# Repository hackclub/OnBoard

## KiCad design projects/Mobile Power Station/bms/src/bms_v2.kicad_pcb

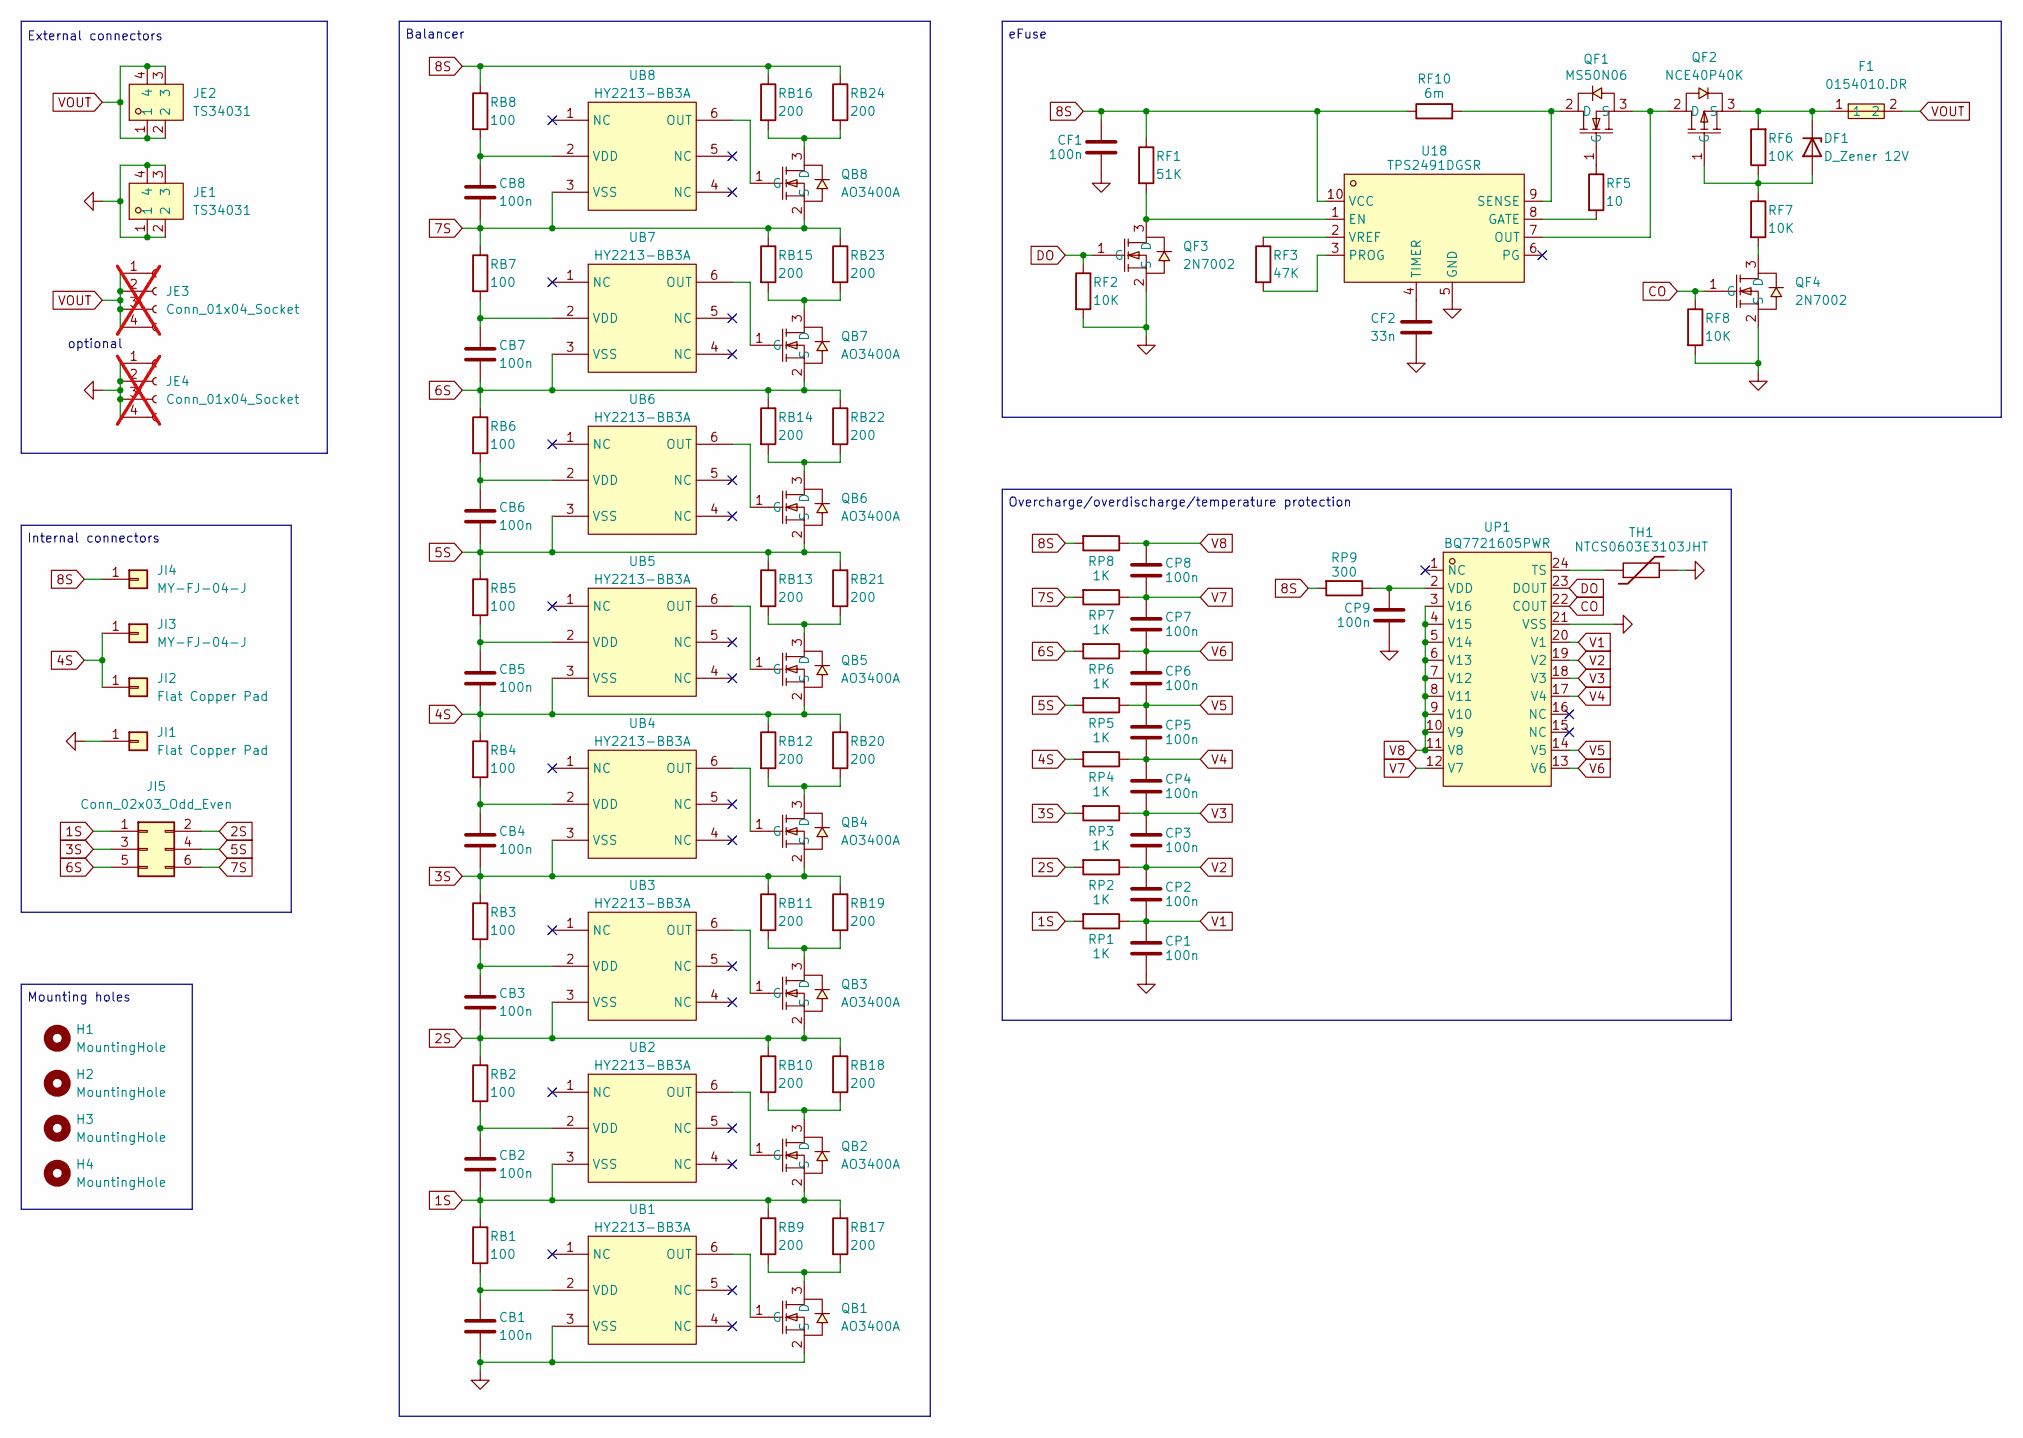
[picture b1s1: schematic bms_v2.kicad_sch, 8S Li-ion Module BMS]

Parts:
CB1, CB2, CB3, CB4, CB5, CB6, CB7, CB8: 100n; C_0603_1608Metric
CF1: 100n; C_0603_1608Metric
CF2: 33n; C_0603_1608Metric
CP1, CP2, CP3, CP4, CP5, CP6, CP7, CP8, CP9: 100n; C_0603_1608Metric
DF1: D_Zener 12V; D_SOD-323
F1: 0154010.DR; FUSE-SMD_L9.7-W5.0; LCSC Part C206921
H1, H2, H3, H4: MountingHole; MountingHole_3mm
JE1, JE2: TS34031; CONN-SMD_TS34031; LCSC Part C481441
JE3, JE4: Conn_01x04_Socket; 4p_BC; not fitted
JI1, JI2: Flat Copper Pad; li-ion 21700 negative terminal contact
JI3, JI4: MY-FJ-04-J; li-ion 21700 positive terminal contact; LCSC Part C5457115
JI5: Conn_02x03_Odd_Even; PinHeader_2x03_P2.54mm_Vertical_SMD
QB1, QB2, QB3, QB4, QB5, QB6, QB7, QB8: AO3400A; SOT-23-3_L2.9-W1.6-P1.90-LS2.8-BR; LCSC Part C20917
QF1: MS50N06; TO-252-2_L6.6-W6.1-P4.57-LS10.0-BR-CW; LCSC Part C2902884
QF2: NCE40P40K; TO-252-2_L6.6-W6.1-P4.57-LS9.9-TL-CW; LCSC Part C130100
QF3, QF4: 2N7002; SOT-23-3_L2.9-W1.3-P1.90-LS2.4-BR; LCSC Part C8545
RB1, RB2, RB3, RB4, RB5, RB6, RB7, RB8: 100; R_0603_1608Metric
RB9, RB10, RB11, RB12, RB13, RB14, RB15, RB16, RB17, RB18, RB19, RB20, RB21, RB22, RB23, RB24: 200; R_0805_2012Metric
RF1: 51K; R_0603_1608Metric
RF2, RF6, RF7, RF8: 10K; R_0603_1608Metric
RF3: 47K; R_0603_1608Metric
RF5: 10; R_0603_1608Metric
RF10: 6m; RES-SMD_L6.4-W3.2-A; LCSC Part C323769
RP1, RP2, RP3, RP4, RP5, RP6, RP7, RP8: 1K; R_0603_1608Metric
RP9: 300; R_0603_1608Metric
TH1: NTCS0603E3103JHT; R_0603_1608Metric; LCSC Part C3028872
U18: TPS2491DGSR; VSSOP-10_L3.0-W3.0-P0.50-LS4.9-BL; LCSC Part C273636
UB1, UB2, UB3, UB4, UB5, UB6, UB7, UB8: HY2213-BB3A; SOT-23-6_L2.9-W1.6-P0.95-LS2.8-BR; LCSC Part C113632
UP1: BQ7721605PWR; TSSOP-24_L7.8-W4.4-P0.65-LS6.4-BL; LCSC Part C2974715

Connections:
1S: CB2.2, JI5.1, QB2.2 (S), RB1.1, RB9.1, RB17.1, RP1.2, UB2.3 (VSS)
2S: CB3.2, JI5.2, QB3.2 (S), RB2.1, RB10.1, RB18.1, RP2.2, UB3.3 (VSS)
3S: CB4.2, JI5.3, QB4.2 (S), RB3.1, RB11.1, RB19.1, RP3.2, UB4.3 (VSS)
4S: CB5.2, JI2.1, JI3.1, QB5.2 (S), RB4.1, RB12.1, RB20.1, RP4.2, UB5.3 (VSS)
5S: CB6.2, JI5.4, QB6.2 (S), RB5.1, RB13.1, RB21.1, RP5.2, UB6.3 (VSS)
6S: CB7.2, JI5.5, QB7.2 (S), RB6.1, RB14.1, RB22.1, RP6.2, UB7.3 (VSS)
7S: CB8.2, JI5.6, QB8.2 (S), RB7.1, RB15.1, RB23.1, RP7.2, UB8.3 (VSS)
8S: CF1.2, JI4.1, RB8.1, RB16.1, RB24.1, RF1.1, RF10.1, RP8.2, RP9.2, U18.10 (VCC)
CO: QF4.1 (G), RF8.1, UP1.22 (COUT)
DO: QF3.1 (G), RF2.1, UP1.23 (DOUT)
GND: CB1.2, CF1.1, CF2.2, CP1.1, CP9.1, JE1.1, JE1.2, JE1.3, JE1.4, JE4.1, JE4.2, JE4.3, JE4.4, JI1.1, QB1.2 (S), QF3.2 (S), QF4.2 (S), RF2.2, RF8.2, TH1.2, U18.5 (GND), UB1.3 (VSS), UP1.21 (VSS)
unnamed: DF1.2 (A), QF2.1 (G), RF6.1, RF7.1
unnamed: DF1.1 (K), F1.1, QF2.3 (S), RF6.2
unnamed: QB1.3 (D), RB9.2, RB17.2
unnamed: QB1.1 (G), UB1.6 (OUT)
unnamed: QB2.3 (D), RB10.2, RB18.2
unnamed: QB2.1 (G), UB2.6 (OUT)
unnamed: QB3.3 (D), RB11.2, RB19.2
unnamed: QB3.1 (G), UB3.6 (OUT)
unnamed: QB4.3 (D), RB12.2, RB20.2
unnamed: QB4.1 (G), UB4.6 (OUT)
unnamed: QB5.3 (D), RB13.2, RB21.2
unnamed: QB5.1 (G), UB5.6 (OUT)
unnamed: QB6.3 (D), RB14.2, RB22.2
unnamed: QB6.1 (G), UB6.6 (OUT)
unnamed: QB7.3 (D), RB15.2, RB23.2
unnamed: QB7.1 (G), UB7.6 (OUT)
unnamed: QB8.3 (D), RB16.2, RB24.2
unnamed: QB8.1 (G), UB8.6 (OUT)
unnamed: QF1.2 (D), RF10.2, U18.9 (SENSE)
unnamed: QF1.1 (G), RF5.1
unnamed: QF1.3 (S), QF2.2 (D), U18.7 (OUT)
unnamed: QF3.3 (D), RF1.2, U18.1 (EN)
unnamed: QF4.3 (D), RF7.2
unnamed: RF5.2, U18.8 (GATE)
unnamed: RF3.2, U18.3 (PROG)
unnamed: CF2.1, U18.4 (TIMER)
unnamed: RF3.1, U18.2 (VREF)
unnamed: CB1.1, RB1.2, UB1.2 (VDD)
unnamed: CB2.1, RB2.2, UB2.2 (VDD)
unnamed: CB3.1, RB3.2, UB3.2 (VDD)
unnamed: CB4.1, RB4.2, UB4.2 (VDD)
unnamed: CB5.1, RB5.2, UB5.2 (VDD)
unnamed: CB6.1, RB6.2, UB6.2 (VDD)
unnamed: CB7.1, RB7.2, UB7.2 (VDD)
unnamed: CB8.1, RB8.2, UB8.2 (VDD)
unnamed: TH1.1, UP1.24 (TS)
unnamed: CP9.2, RP9.1, UP1.2 (VDD)
V1: CP1.2, CP2.1, RP1.1, UP1.20 (V1)
V2: CP2.2, CP3.1, RP2.1, UP1.19 (V2)
V3: CP3.2, CP4.1, RP3.1, UP1.18 (V3)
V4: CP4.2, CP5.1, RP4.1, UP1.17 (V4)
V5: CP5.2, CP6.1, RP5.1, UP1.14 (V5)
V6: CP6.2, CP7.1, RP6.1, UP1.13 (V6)
V7: CP7.2, CP8.1, RP7.1, UP1.12 (V7)
V8: CP8.2, RP8.1, UP1.3 (V16), UP1.4 (V15), UP1.5 (V14), UP1.6 (V13), UP1.7 (V12), UP1.8 (V11), UP1.9 (V10), UP1.10 (V9), UP1.11 (V8)
VOUT: F1.2, JE2.1, JE2.2, JE2.3, JE2.4, JE3.1, JE3.2, JE3.3, JE3.4

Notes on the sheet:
Balancer
optional
Internal connectors
External connectors
Overcharge/overdischarge/temperature protection
Mounting holes
eFuse

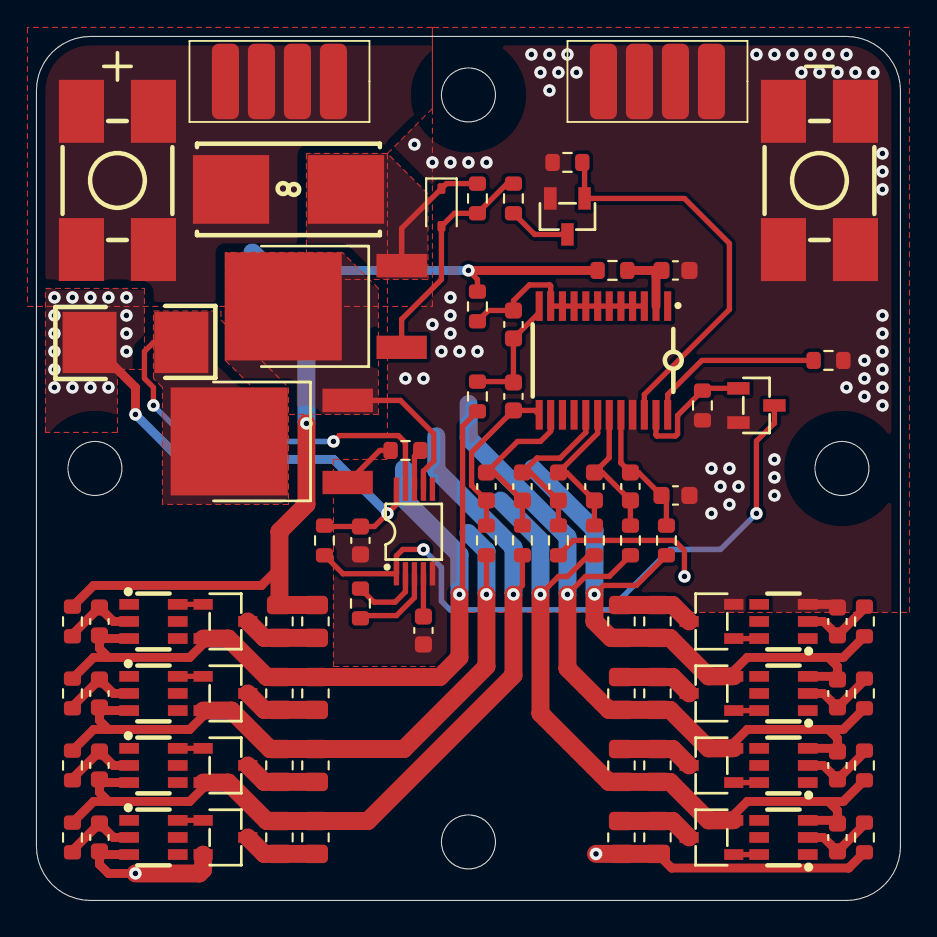
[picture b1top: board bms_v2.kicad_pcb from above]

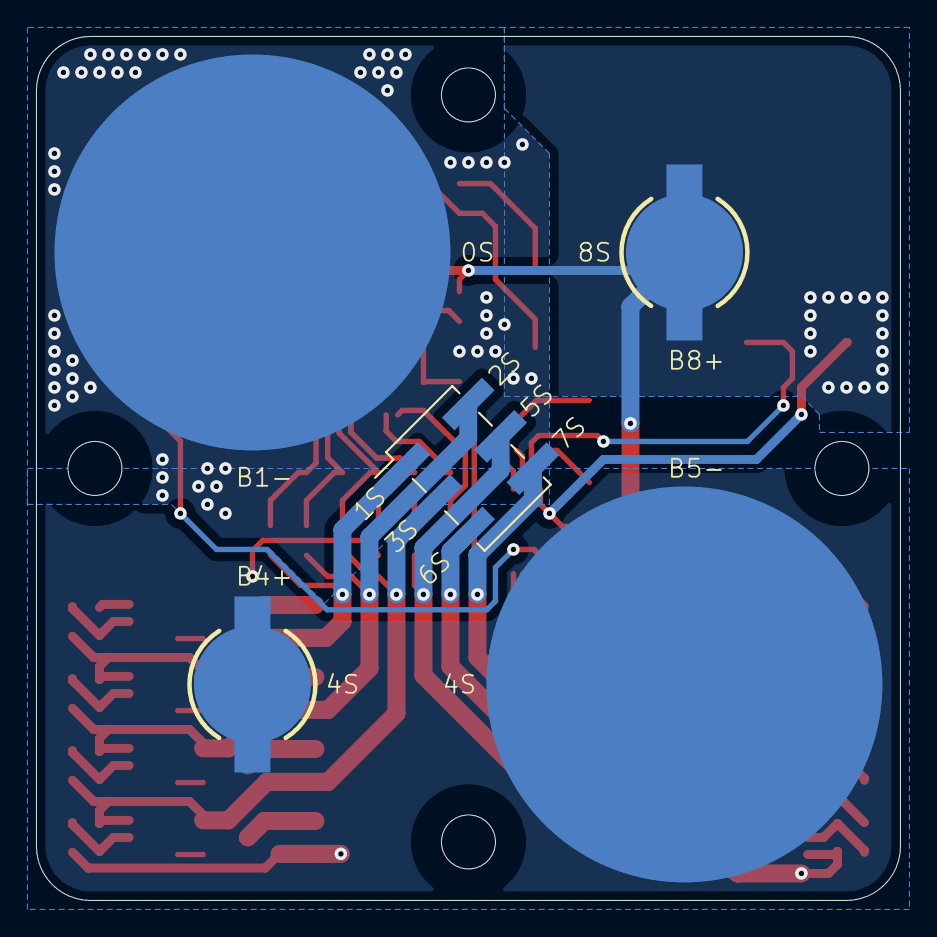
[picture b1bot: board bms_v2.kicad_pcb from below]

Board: 2 copper layers, 48.0 x 48.0 mm, 98 parts (5 on the bottom side), 57 nets.

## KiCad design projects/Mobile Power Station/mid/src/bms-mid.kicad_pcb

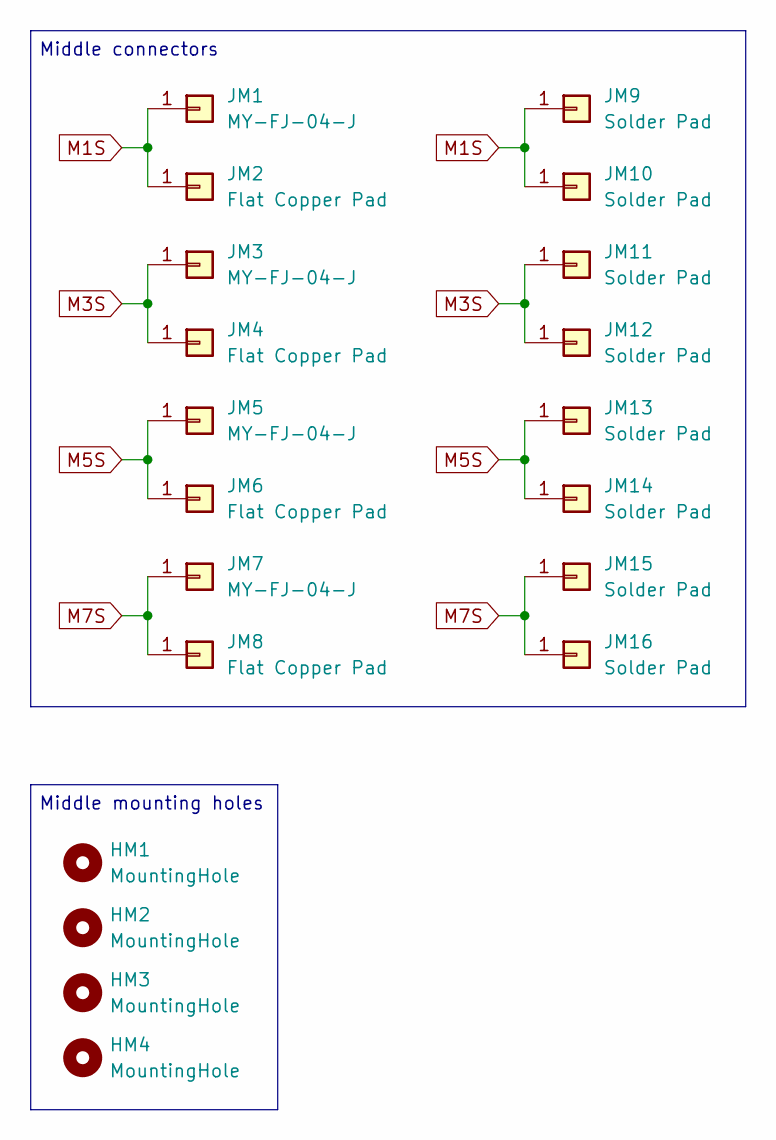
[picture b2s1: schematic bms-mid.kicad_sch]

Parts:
HM1, HM2, HM3, HM4: MountingHole; MountingHole_3mm
JM1, JM3, JM5, JM7: MY-FJ-04-J; li-ion 21700 positive terminal contact; LCSC Part C5457115
JM2, JM4, JM6, JM8: Flat Copper Pad; li-ion 21700 negative terminal contact
JM9, JM10, JM11, JM12, JM13, JM14, JM15, JM16: Solder Pad; SolderWirePad_1x01_SMD_1x2mm

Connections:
M1S: JM1.1, JM2.1, JM9.1, JM10.1
M3S: JM3.1, JM4.1, JM11.1, JM12.1
M5S: JM5.1, JM6.1, JM13.1, JM14.1
M7S: JM7.1, JM8.1, JM15.1, JM16.1

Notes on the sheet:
Middle mounting holes
Middle connectors

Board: 2 copper layers, 20 parts (8 on the bottom side), 4 nets, no tracks yet.

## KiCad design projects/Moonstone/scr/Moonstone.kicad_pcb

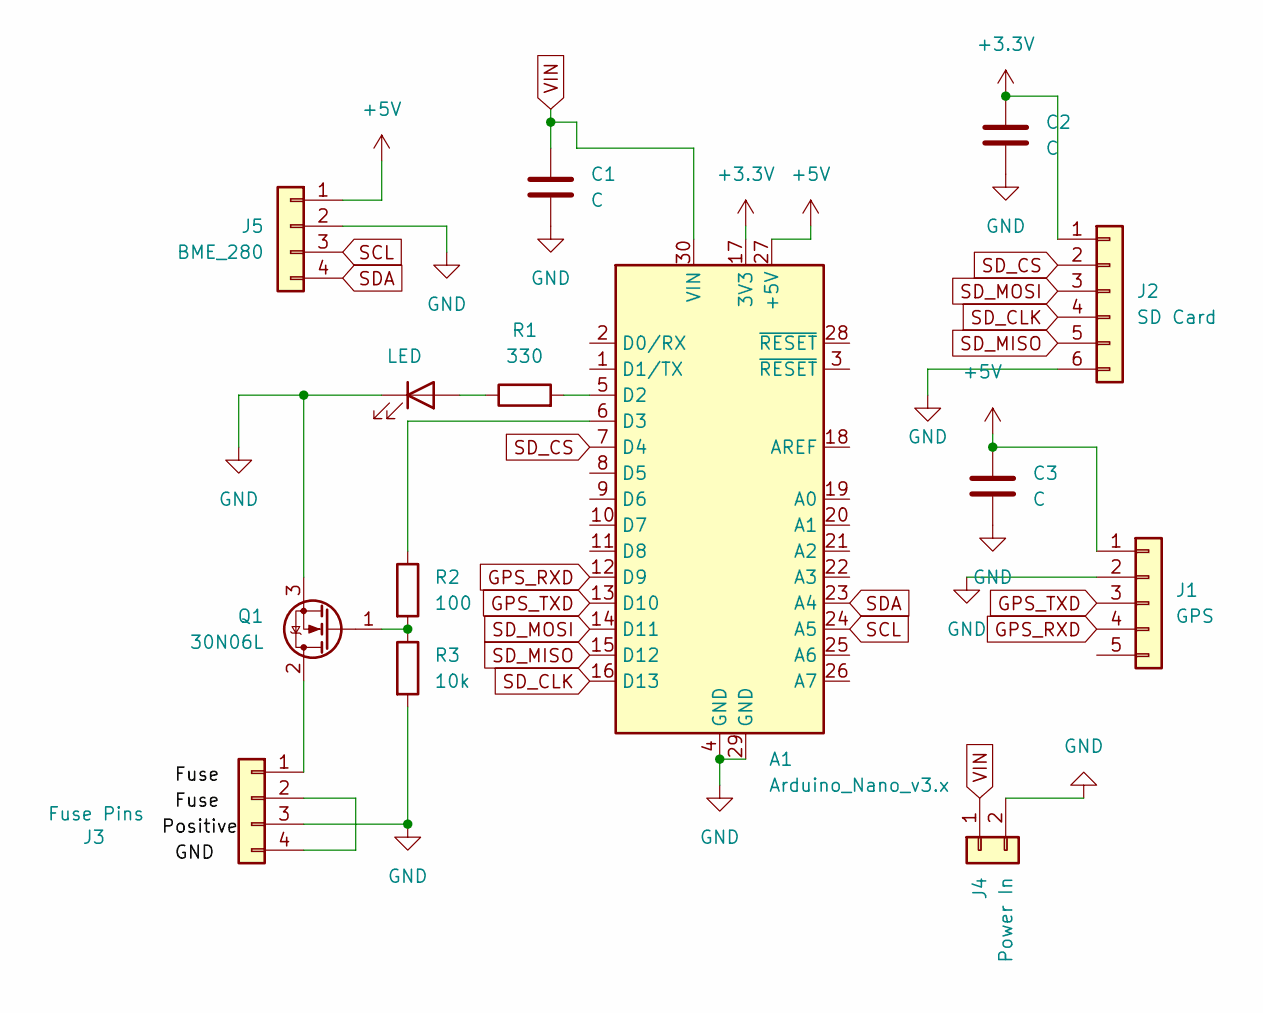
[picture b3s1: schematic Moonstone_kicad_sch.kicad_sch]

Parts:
A1: Arduino_Nano_v3.x; Arduino_Nano
C1, C2, C3: C; C_0805_2012Metric_Pad1.18x1.45mm_HandSolder
D1: LED; LED_0805_2012Metric_Pad1.15x1.40mm_HandSolder
J1: GPS; PinHeader_1x05_P2.54mm_Vertical
J2: SD Card; PinHeader_1x06_P2.54mm_Vertical
J3: Fuse Pins; PinHeader_1x04_P2.54mm_Vertical
J4: Power In; PinHeader_1x02_P2.54mm_Vertical
J5: BME_280; PinHeader_1x04_P2.54mm_Vertical
Q1: 30N06L; PinHeader_1x03_P2.54mm_Vertical
R1: 330; R_0402_1005Metric_Pad0.72x0.64mm_HandSolder
R2: 100; R_0402_1005Metric_Pad0.72x0.64mm_HandSolder
R3: 10k; R_0402_1005Metric_Pad0.72x0.64mm_HandSolder

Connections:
+3.3V: A1.17 (3V3), C2.1, J2.1
+5V: A1.27 (+5V), C3.1, J1.1, J5.1
GND: A1.4 (GND), A1.29 (GND), C1.2, C2.2, C3.2, D1.1 (K), J1.2, J2.6, J3.3, J4.2, J5.2, Q1.3 (S), R3.2
GPS_RXD: A1.12 (D9), J1.4
GPS_TXD: A1.13 (D10), J1.3
unnamed: A1.5 (D2), R1.2
unnamed: A1.6 (D3), R2.1
unnamed: D1.2 (A), R1.1
unnamed: J3.1, Q1.2 (D)
unnamed: J3.2, J3.4
unnamed: Q1.1 (G), R2.2, R3.1
SCL: A1.24 (A5), J5.3
SDA: A1.23 (A4), J5.4
SD_CLK: A1.16 (D13), J2.4
SD_CS: A1.7 (D4), J2.2
SD_MISO: A1.15 (D12), J2.5
SD_MOSI: A1.14 (D11), J2.3
VIN: A1.30 (VIN), C1.1, J4.1

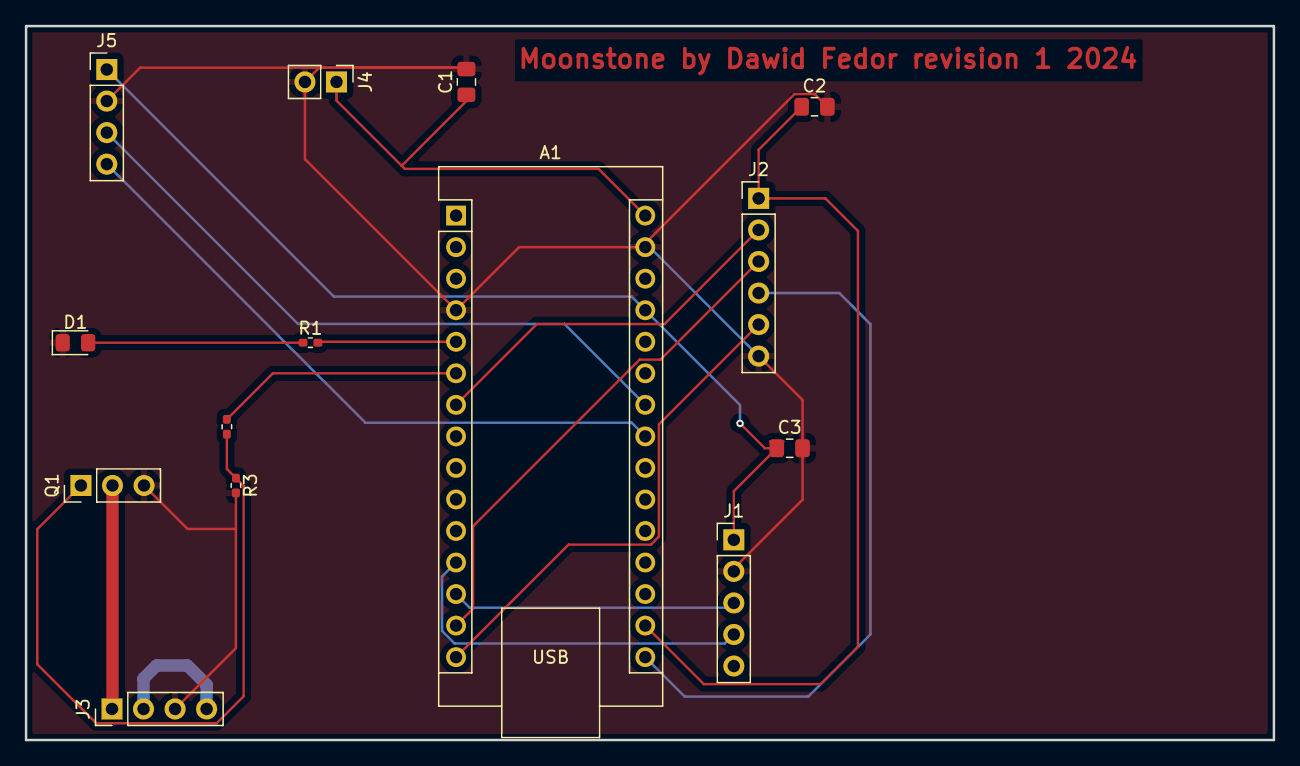
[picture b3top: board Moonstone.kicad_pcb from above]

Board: 2 copper layers, 100.5 x 57.5 mm, 14 parts (0 on the bottom side), 18 nets.

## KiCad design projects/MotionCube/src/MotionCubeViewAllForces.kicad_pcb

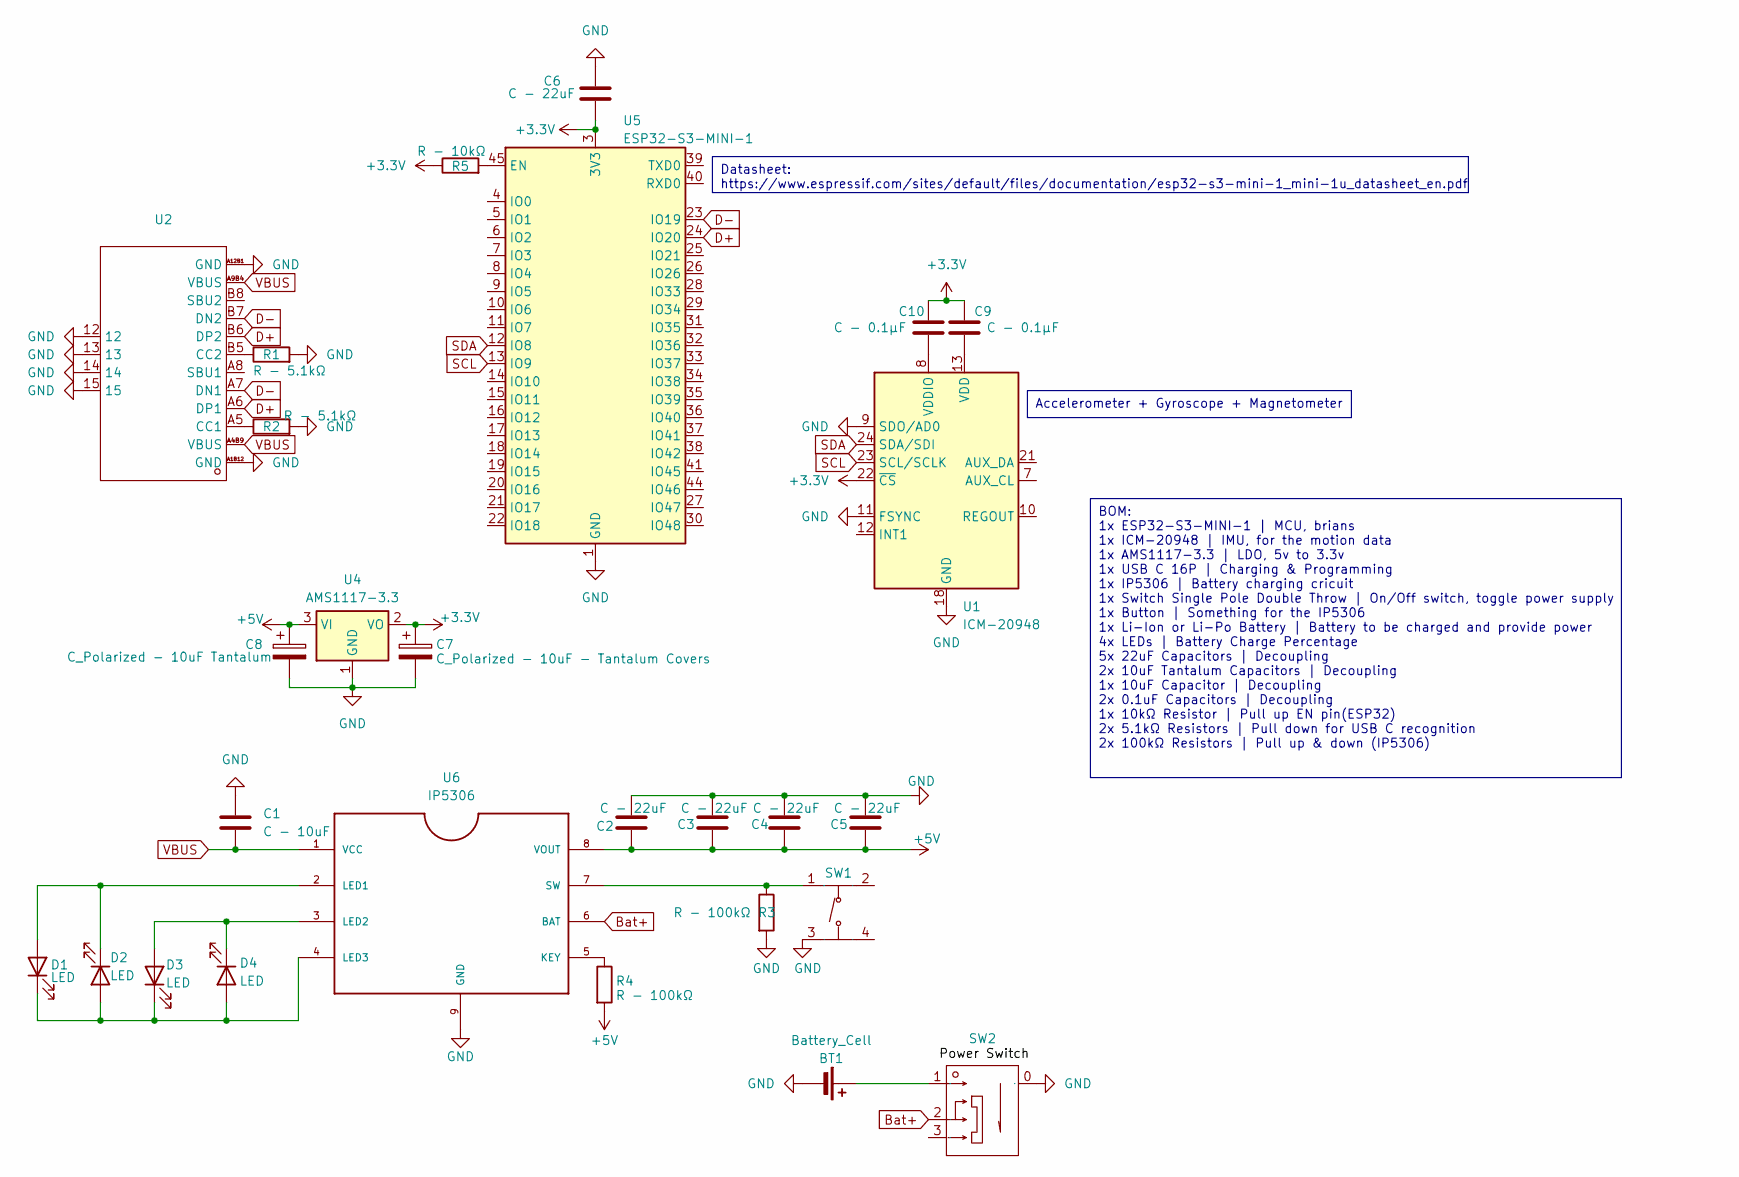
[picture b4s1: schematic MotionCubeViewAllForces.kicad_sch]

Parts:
BT1: Battery_Cell; TestPoint_2Pads_Pitch5.08mm_Drill1.3mm
C1: C - 10uF; C_0201_0603Metric_Pad0.64x0.40mm_HandSolder
C2, C3, C4, C5, C6: C - 22uF; C_0603_1608Metric_Pad1.08x0.95mm_HandSolder
C7: C_Polarized - 10uF - Tantalum Covers; CP_EIA-3216-18_Kemet-A_Pad1.58x1.35mm_HandSolder
C8: C_Polarized - 10uF Tantalum; CP_EIA-3216-18_Kemet-A_Pad1.58x1.35mm_HandSolder
C9, C10: C - 0.1µF; C_0402_1005Metric_Pad0.74x0.62mm_HandSolder
D1, D2, D3, D4: LED; LED_0805_2012Metric_Pad1.15x1.40mm_HandSolder
R1, R2: R - 5.1kΩ; R_0603_1608Metric_Pad0.98x0.95mm_HandSolder
R3, R4: R - 100kΩ; R_0402_1005Metric_Pad0.72x0.64mm_HandSolder
R5: R - 10kΩ; R_1206_3216Metric_Pad1.30x1.75mm_HandSolder
SW1: SW-SMD_4P-L5.1-W5.1-P3.70-LS6.5-TL_H1.5; Manufacturer Part TS-1187A-B-A-B; LCSC Part Name 5.1*5.1*1.5mm 立贴 轻触开关
SW2: SW-SMD_3P-P1.50_L2.7-W6.6; Manufacturer Part SK-3296S-01-L1; LCSC Part Name 柄长1.5mm 卧贴双档 滑动开关
U1: ICM-20948; InvenSense_QFN-24_3x3mm_P0.4mm
U2: USB-C-SMD_YTC-TC16S-24; Manufacturer Part YTC-TC16S-24; LCSC Part Name Type-C 母 卧贴
U4: AMS1117-3.3; SOT-223-3_TabPin2
U5: ESP32-S3-MINI-1; ESP32-S2-MINI-1
U6: IP5306; SOIC9P127_490X600X170L84X42T330X241N

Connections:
+3.3V: C6.1, C7.1, C9.1, C10.2, R5.1, U1.22 (~CS), U4.2 (VO), U5.3 (3V3)
+5V: C2.1, C3.1, C4.1, C5.1, C8.1, R4.2, U4.3 (VI), U6.8 (VOUT)
Bat+: SW2.2, U6.6 (BAT)
D+: U2.A6 (DP1), U2.B6 (DP2), U5.24 (IO20)
D-: U2.A7 (DN1), U2.B7 (DN2), U5.23 (IO19)
GND: BT1.2 (-), C1.2, C2.2, C3.2, C4.2, C5.2, C6.2, C7.2, C8.2, R1.2, R2.2, R3.2, SW1.3 (C), SW2.0, U1.9 (SDO/AD0), U1.11 (FSYNC), U1.18 (GND), U1.20 (GND), U2.12, U2.13, U2.14, U2.15, U2.A1B12 (GND), U2.A12B1 (GND), U4.1 (GND), U5.1 (GND), U5.2 (GND), U5.42 (GND), U5.43 (GND), U5.46 (GND), U5.47 (GND), U5.48 (GND), U5.49 (GND), U5.50 (GND), U5.51 (GND), U5.52 (GND), U5.53 (GND), U5.54 (GND), U5.55 (GND), U5.56 (GND), U5.57 (GND), U5.58 (GND), U5.59 (GND), U5.60 (GND), U5.61 (GND), U5.62 (GND), U5.63 (GND), U5.64 (GND), U5.65 (GND), U6.9 (GND)
unnamed: BT1.1 (+), SW2.1
unnamed: D1.2 (A), D2.1 (K), U6.2 (LED1)
unnamed: D1.1 (K), D2.2 (A), D3.1 (K), D4.2 (A), U6.4 (LED3)
unnamed: D3.2 (A), D4.1 (K), U6.3 (LED2)
unnamed: R3.1, SW1.1 (A), U6.7 (SW)
unnamed: C9.2, U1.13 (VDD)
unnamed: C10.1, U1.8 (VDDIO)
unnamed: R2.1, U2.A5 (CC1)
unnamed: R1.1, U2.B5 (CC2)
unnamed: R5.2, U5.45 (EN)
unnamed: R4.1, U6.5 (KEY)
SCL: U1.23 (SCL/SCLK), U5.13 (IO9)
SDA: U1.24 (SDA/SDI), U5.12 (IO8)
VBUS: C1.1, U2.A4B9 (VBUS), U2.A9B4 (VBUS), U6.1 (VCC)

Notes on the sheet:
BOM: 1x ESP32-S3-MINI-1 | MCU, brians 1x ICM-20948 | IMU, for the motion data 1x AMS1117-3.3 | LDO, 5v to 3.3v 1x USB C 16P | Charging & Programming 1x IP5306 | Battery charging cricuit 1x Switch Single Pole Double Throw | On/Off switch, toggle power supply 1x Button | Something for the IP5306 1x L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
Accelerometer + Gyroscope + Magnetometer
Datasheet: https://www.espressif.com/sites/default/files/documentation/esp32-s3-mini-1_mini-1u_datasheet_en.pdf

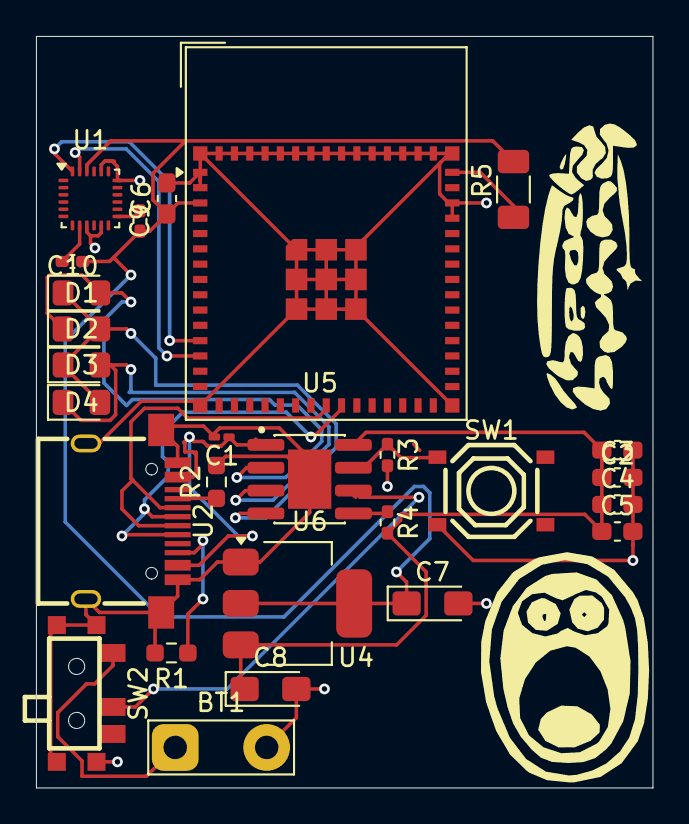
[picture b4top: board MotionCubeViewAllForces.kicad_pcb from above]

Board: 2 copper layers, 34.2 x 41.8 mm, 27 parts (0 on the bottom side), 20 nets.

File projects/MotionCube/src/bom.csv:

Designator,Footprint,Quantity,Value,LCSC Part #
BT1,TestPoint_2Pads_Pitch5.08mm_Drill1.3mm,1,Battery_Cell,
C1,0201,1,C - 10uF,
"C10, C9",0402,2,C - 0.1µF,
"C2, C3, C4, C5, C6",0603,5,C - 22uF,
C7,CP_EIA-3216-18_Kemet-A_Pad1.58x1.35mm_HandSolder,1,C_Polarized -  10uF -  Tantalum Covers,
C8,CP_EIA-3216-18_Kemet-A_Pad1.58x1.35mm_HandSolder,1,C_Polarized - 10uF Tantalum,
"D1, D2, D3, D4",0805,4,LED,
"R1, R2",0603,2,R - 5.1kΩ,
"R3, R4",0402,2,R - 100kΩ,
R5,1206,1,R - 10kΩ,
SW1,SW-SMD_4P-L5.1-W5.1-P3.70-LS6.5-TL_H1.5,1,~,
SW2,SW-SMD_3P-P1.50_L2.7-W6.6,1,~,
U1,InvenSense_QFN-24_3x3mm_P0.4mm,1,ICM-20948,
U2,USB-C-SMD_YTC-TC16S-24,1,~,
U4,SOT-223-3_TabPin2,1,AMS1117-3.3,
U5,ESP32-S2-MINI-1,1,ESP32-S3-MINI-1,
U6,SOIC9P127_490X600X170L84X42T330X241N,1,IP5306,

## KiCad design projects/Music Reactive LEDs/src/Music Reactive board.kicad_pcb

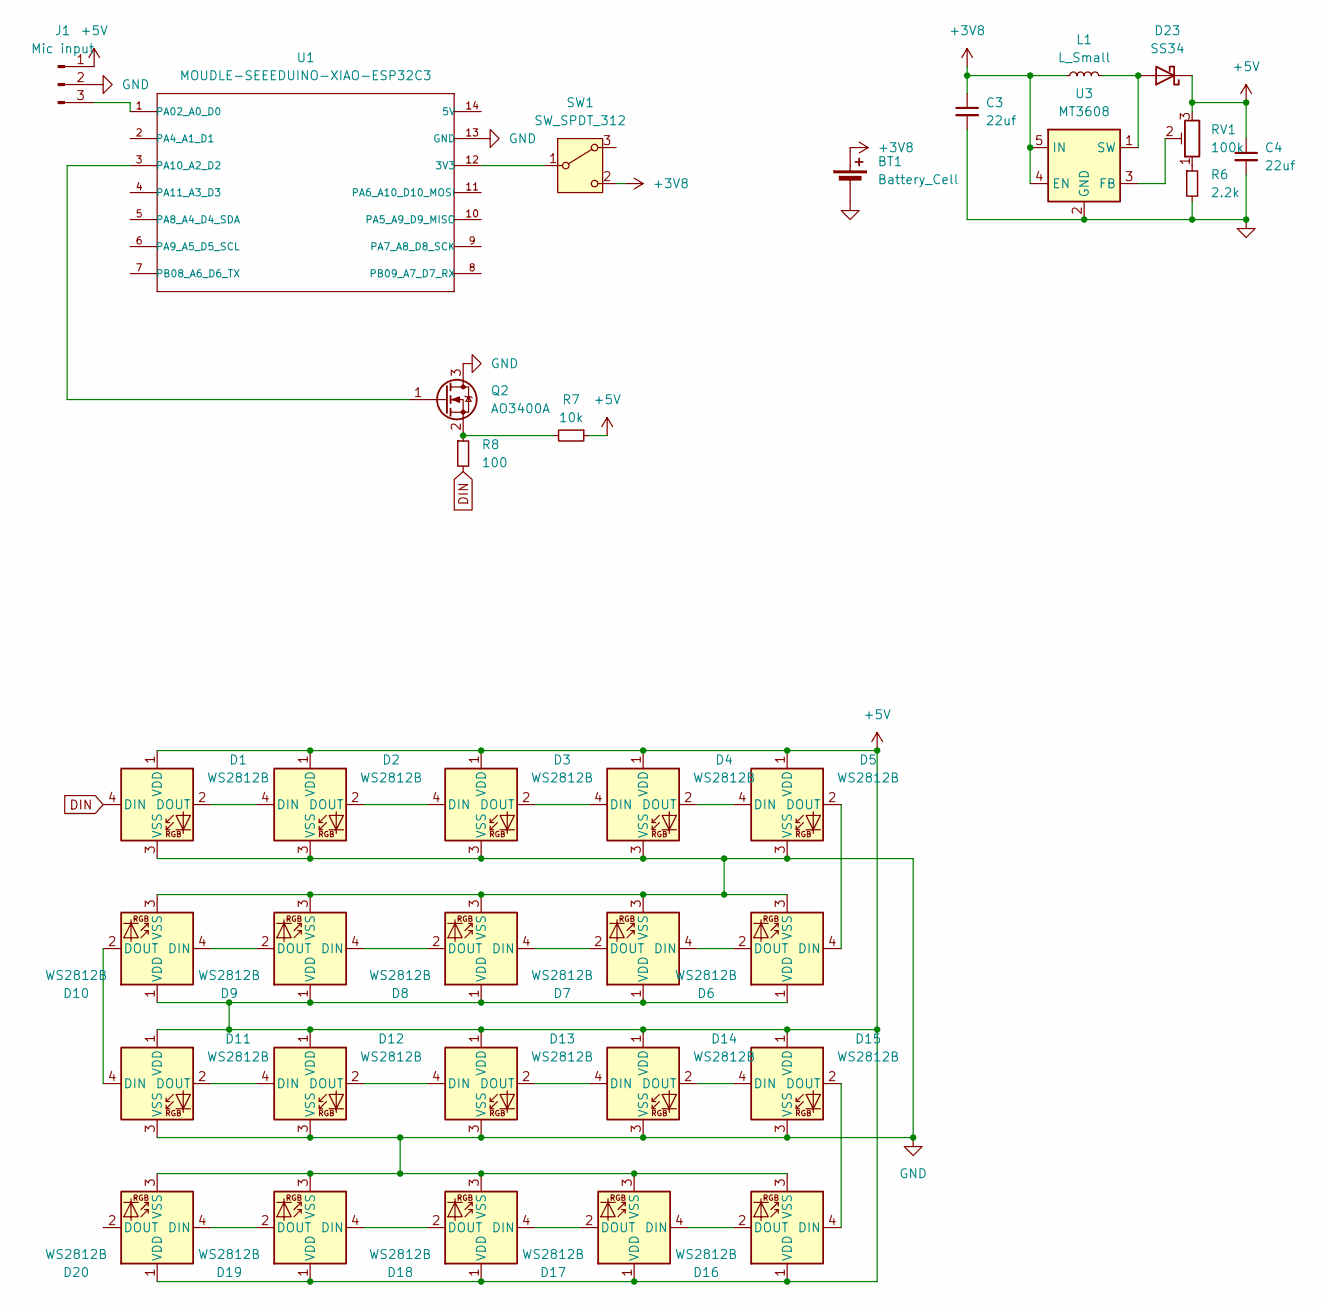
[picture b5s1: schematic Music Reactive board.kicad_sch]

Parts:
BT1: Battery_Cell; Battery_Panasonic_CR2032-HFN_Horizontal_CircularHoles
C3, C4: 22uf; C_0805_2012Metric
D1, D2, D3, D4, D5, D6, D7, D8, D9, D10, D11, D12, D13, D14, D15, D16, D17, D18, D19, D20: WS2812B; LED_WS2812B_PLCC4_5.0x5.0mm_P3.2mm
D23: SS34; D_SMA
J1: Mic input; PinHeader_1x03_P2.54mm_Vertical
L1: L_Small; L_10.4x10.4_H4.8
Q2: AO3400A; SOT-23
R6: 2.2k; R_0805_2012Metric_Pad1.20x1.40mm_HandSolder
R7: 10k; R_0805_2012Metric_Pad1.20x1.40mm_HandSolder
R8: 100; R_0805_2012Metric_Pad1.20x1.40mm_HandSolder
RV1: 100k; Potentiometer_Bourns_TC33X_Vertical
SW1: SW_SPDT_312; SW_DIP_SPSTx01_Slide_6.7x4.1mm_W6.73mm_P2.54mm_LowProfile_J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
U1: MOUDLE-SEEEDUINO-XIAO-ESP32C3; XIAO-Generic-Thruhole-14P-2.54-21X17.8MM
U3: MT3608; SOT-23-6

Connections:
+3V8: BT1.1 (+), C3.1, L1.1, SW1.2 (C), U3.4 (EN), U3.5 (IN)
+5V: C4.1, D1.1 (VDD), D2.1 (VDD), D3.1 (VDD), D4.1 (VDD), D5.1 (VDD), D6.1 (VDD), D7.1 (VDD), D8.1 (VDD), D9.1 (VDD), D10.1 (VDD), D11.1 (VDD), D12.1 (VDD), D13.1 (VDD), D14.1 (VDD), D15.1 (VDD), D16.1 (VDD), D17.1 (VDD), D18.1 (VDD), D19.1 (VDD), D20.1 (VDD), D23.1 (K), J1.1, R7.1, RV1.3
DIN: D1.4 (DIN), R8.2
GND: BT1.2 (-), C3.2, C4.2, D1.3 (VSS), D2.3 (VSS), D3.3 (VSS), D4.3 (VSS), D5.3 (VSS), D6.3 (VSS), D7.3 (VSS), D8.3 (VSS), D9.3 (VSS), D10.3 (VSS), D11.3 (VSS), D12.3 (VSS), D13.3 (VSS), D14.3 (VSS), D15.3 (VSS), D16.3 (VSS), D17.3 (VSS), D18.3 (VSS), D19.3 (VSS), D20.3 (VSS), J1.2, Q2.3 (D), R6.2, U1.13 (GND), U3.2 (GND)
unnamed: D1.2 (DOUT), D2.4 (DIN)
unnamed: D2.2 (DOUT), D3.4 (DIN)
unnamed: D3.2 (DOUT), D4.4 (DIN)
unnamed: D4.2 (DOUT), D5.4 (DIN)
unnamed: D5.2 (DOUT), D6.4 (DIN)
unnamed: D6.2 (DOUT), D7.4 (DIN)
unnamed: D7.2 (DOUT), D8.4 (DIN)
unnamed: D8.2 (DOUT), D9.4 (DIN)
unnamed: D9.2 (DOUT), D10.4 (DIN)
unnamed: D10.2 (DOUT), D11.4 (DIN)
unnamed: D11.2 (DOUT), D12.4 (DIN)
unnamed: D12.2 (DOUT), D13.4 (DIN)
unnamed: D13.2 (DOUT), D14.4 (DIN)
unnamed: D14.2 (DOUT), D15.4 (DIN)
unnamed: D15.2 (DOUT), D16.4 (DIN)
unnamed: D16.2 (DOUT), D17.4 (DIN)
unnamed: D17.2 (DOUT), D18.4 (DIN)
unnamed: D18.2 (DOUT), D19.4 (DIN)
unnamed: D19.2 (DOUT), D20.4 (DIN)
unnamed: D23.2 (A), L1.2, U3.1 (SW)
unnamed: J1.3, U1.1 (PA02_A0_D0)
unnamed: Q2.1 (G), U1.3 (PA10_A2_D2)
unnamed: Q2.2 (S), R7.2, R8.1
unnamed: R6.1, RV1.1
unnamed: SW1.1 (B), U1.12 (3V3)
unnamed: RV1.2, U3.3 (FB)

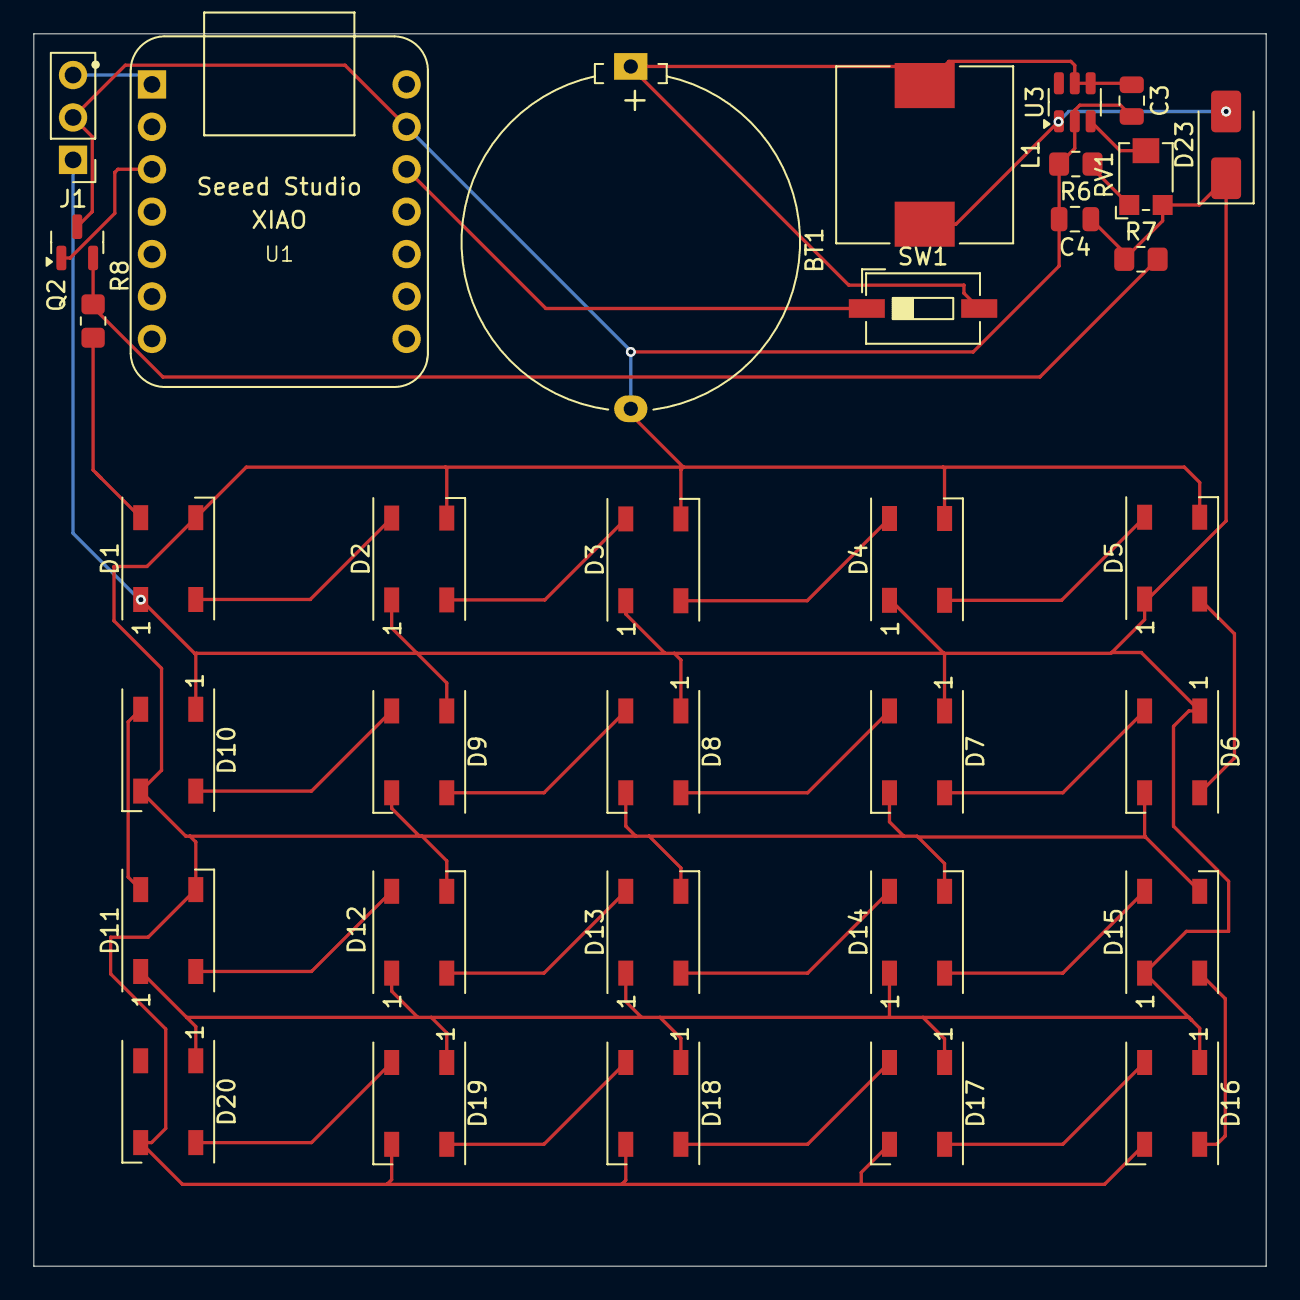
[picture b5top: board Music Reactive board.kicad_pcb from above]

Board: 2 copper layers, 73.8 x 73.8 mm, 34 parts (0 on the bottom side), 30 nets.

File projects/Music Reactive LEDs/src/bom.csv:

Designator,Footprint,Quantity,Value,LCSC Part #
BT1,Battery_Panasonic_CR2032-HFN_Horizontal_CircularHoles,1,Battery_Cell,
"C3, C4",805,2,22uf,C45783
"D1, D10, D11, D12, D13, D14, D15, D16, D17, D18, D19, D2, D20, D3, D4, D5, D6, D7, D8, D9",LED_WS2812B_PLCC4_5.0x5.0mm_P3.2mm,20,WS2812B,C22461793
D23,D_SMA,1,SS34,C8678
J1,PinHeader_1x03_P2.54mm_Vertical,1,Conn_01x03_Pin,
L1,L_10.4x10.4_H4.8,1,L_Small,C10165
Q2,SOT-23,1,AO3400A,C20917
R6,805,1,2.2k,C17520
R7,805,1,10k,C17414
R8,805,1,100,C17408
RV1,Potentiometer_Bourns_TC33X_Vertical,1,100k,C719186
SW1,SW_DIP_SPSTx01_Slide_6.7x4.1mm_W6.73mm_P2.54mm_LowProfile_JPin,1,SW_SPDT_312,
U1,XIAO-Generic-Thruhole-14P-2.54-21X17.8MM,1,MOUDLE-SEEEDUINO-XIAO-ESP32C3,
U3,SOT-23-6,1,MT3608,C84817
